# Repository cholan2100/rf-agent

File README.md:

# RF Agent

An autonomous AI RF/Microwave hardware engineering engine and PCB design suite.

> [!IMPORTANT]
> **AI Harness Native**: This project is explicitly designed to be used inside an AI Agent Harness environment (such as Google's Antigravity, Cursor, Claude Code, GitHub Copilot Workspace, OpenDevin, etc.). 
> 
> **Intended Workflow**:
> 1. Check out this repository inside your AI harness.
> 2. Ask the harness agent to design an RF PCB (e.g., "Design a 10dB 2.4GHz Attenuator").
> 3. The agent will read the provided instructions (`AGENTS.md` / `SKILLS.md`), follow the 9-stage engineering protocol, and synthesize the schematics, route the layout, and run the simulations autonomously.

`rf-agent` enables AI coding agents to autonomously synthesize schematics, route controlled-impedance coplanar waveguides, perform headless DRC verification, execute 3D electromagnetic FDTD simulations, and generate production-ready Gerber archives and raytraced 3D visualizations.

---

## Quickstart

In your preferred AI agent harness (Antigravity, Cursor, Claude Code, OpenCode, Codex, GitHub Copilot, Windsurf, Roo Code), paste the following prompt into the chat:

```text
Clone https://github.com/cholan2100/rf-agent.git with submodules and Initialize the agent as per governing files in this repository.
```

> [!TIP]
> If you have already cloned the repository and opened the workspace folder inside your harness, you can simply prompt:
> ```text
> Initialize the agent as per governing files in this repository.
> ```

---

## How it Works

The autonomous RF hardware engineering pipeline operates as a synergistic triad:

* **AI Agent Harness**: Provides intelligence using any LLM model (e.g., Claude, Gemini, GPT, DeepSeek) within your environment (such as Antigravity, Cursor, Claude Code, OpenCode, Codex, GitHub Copilot, Roo Code).
* **`rf-agent` (This Repository)**: Guides the Agent to execute the engineering workflow step by step per governing protocols (`AGENTS.md` / `SKILLS.md`), synthesizing schematics, calculating passive component values, and formulating controlled-impedance layout specifications.
* **`rf-suite` (Cloud SaaS or Local Dockerized)**: Provides the tools necessary to do the tasks—supplying headless KiCad 10, FreeCAD 1.0, openEMS 3D FDTD, Qucsator-RF, and ngspice solvers either via the hosted AWS SaaS microservice (`http://rf.nakedcircuits.com:8000`) or inside a local Docker container.

---

## Toolchain Architecture: Dependency on `rf-suite`

`rf-agent` is structured as a decoupled, two-tier architecture separating **AI Agent Design Intellect** from the **Heavy EDA & Solver Toolchain**:

```
┌────────────────────────────────────────────────────────────────────────┐
│                          rf-agent (This Repo)                          │
│                   AI Agent Intellect & Workflow Core                   │
│  - Circuit Spec Synthesis (spec.py) & Passive Math (Pi, Tank, BPF, SOLT)│
│  - Programmatic KiCad 10 Schematic & Layout Routing (agent/pcb_gen.py) │
│  - Controlled-Impedance CPWG Math, Tapers, & Via Fencing Synthesis     │
│  - Automated Headless 9-Stage Pipeline Orchestrator (agent/workflow.py) │
│  - Interactive Human-in-the-Loop Review Protocols & Popups             │
└───────────────────────────────────┬────────────────────────────────────┘
                                    │ invokes via rf-suite/bin launchers
                                    ▼
┌────────────────────────────────────────────────────────────────────────┐
│                        rf-suite (Linked Submodule)                     │
│               Containerized Multi-Physics Engineering Stack            │
│  - KiCad 10.0.4: pcbnew Python C++ bindings, kicad-cli, 3D Raytracer   │
│  - FreeCAD 1.0.0: FreeCADCmd, Microwave Workbench, STEP Exporter      │
│  - openEMS v0.37.0-rc2: 3D FDTD Full-Wave EM Solver & CSXCAD API       │
│  - Qucs-S 24.4.1 & qucsator-rf 1.0.3: Linear S-Parameter Co-Simulation │
│  - ngspice 44.2: Non-linear SPICE DC bias & transient sweeps           │
│  - RF Python Stack: scikit-rf, numpy, scipy, matplotlib, cairosvg      │
│  - X11 / noVNC Web Desktop: Interactive visual GUI on port 6080       │
└────────────────────────────────────────────────────────────────────────┘
```

The underlying toolchain is linked as a Git submodule at `./rf-suite` pointing to [`cholan2100/rf-suite`](https://github.com/cholan2100/rf-suite). This guarantees that neither developers nor autonomous agents need to manually compile or install gigabytes of complex C++ EDA tools on the host system.

---

## Docker Environment & Host OS Architecture

The Docker container daemon location depends on the host operating system:
- **Windows**: Docker is by default found and hosted inside the **WSL Debian** environment (`wsl -d Debian`). When running Docker commands directly on Windows, execute them via WSL: `wsl -d Debian bash -c "docker ..."`. The Windows batch scripts in `rf-suite\bin\` (`rf-run.bat`, `rf-bash.bat`, `rf-gui.bat`) automatically detect this and target the WSL Debian container environment.
- **Linux**: Docker is typically native and accessible directly in the standard system PATH (`docker ...`).

---

## Repository Self-Provisioning Protocol for Agents

Autonomous agents and automated CI runners must adhere to the **Turn 0 Self-Provisioning Protocol** (canonical, detailed version: [`AGENTS.md` §1.2](AGENTS.md)):

0. **Step 0 — Automatic `.env` Bootstrapping**:
   If `.env` does not exist (e.g. fresh clone), the agent automatically creates it configured for the local containerized toolchain with **zero AWS credentials**:
   ```ini
   # RF Agent Toolchain Configuration
   RF_BACKEND=local
   RF_SAAS_URL=http://rf.nakedcircuits.com:8000
   RF_WAKE_URL=https://rfhealth.nakedcircuits.com
   ```
   Users do not need to configure AWS credentials. When the local Docker toolchain is active, all solvers run locally inside `rf-suite`.

1. **Gate 1 — Submodule Initialization**:
   A fresh `git clone` does **not** check out submodules by default, so `rf-suite/` will be empty and the launchers will be missing. Verify and bootstrap:
   ```bash
   # Verify (portable, non-fatal):
   git submodule status rf-suite   # must NOT start with a '-'
   # Or check for the launcher directly:
   ls rf-suite/bin/rf-run          # Windows: ls rf-suite\bin\rf-run.bat

   # If missing, initialize and verify:
   git submodule update --init --recursive
   ```
   > Tip for users: cloning with `git clone --recurse-submodules https://github.com/cholan2100/rf-agent.git` pre-satisfies Gate 1.

2. **Gate 2 — Execution Backend Readiness Verification**:
   The default execution backend is **Direct Local Commands** (`RF_BACKEND=local`), running KiCad 10, FreeCAD 1.0, openEMS, and Qucsator inside the containerized `rf-suite` Docker environment.
   - **SaaS Availability Probe**: The agent checks if the cloud SaaS API service (`http://rf.nakedcircuits.com:8000/health`) is online and healthy.
   - **If the SaaS API service is unavailable**: The agent does **not** use or announce the SaaS service to the user, and silently defaults directly to the local dockerized `rf-suite` (`RF_BACKEND=local`).
   - **If the SaaS API service is verified online & healthy**: The agent may offer the option to offload compute via cloud SaaS (`RF_BACKEND=aws_saas`).

   If Direct Local execution is chosen and the Docker image is missing, the agent triggers the build:
   ```bash
   # On Windows (Docker in WSL Debian): compute the WSL path of <repo-root> first
   # (e.g. D:\Workspace\rf\rf-agent -> /mnt/d/Workspace/rf/rf-agent), then:
   wsl -d Debian bash -c "cd <wsl-path-of-repo-root>/rf-suite && docker compose build"
   # Or if native Docker CLI is in Windows PATH:
   cd rf-suite && docker compose build

   # On Linux (Native Docker):
   cd rf-suite && docker compose build
   ```
   When the build finishes, the agent notifies the user:
   > *"The `rf-suite` Docker environment has been built and verified! Proceeding to Gate 3..."*

3. **Gate 3 — Mandatory Final Invitation Greeting**:
   Once Gates 1 and 2 pass:
   - **Every time the repository is used to initialize the agent**, the agent concludes its initialization turn by presenting the final invitation greeting asking what RF circuit to design today, with concrete example prompts (e.g. *"Bandpass filter for 98mhz FM Radio band using parallel LC tank"*, *"Low Noise amplifier for 137MHz satellite band"*, 10dB attenuator, 50Ω calibration load, etc.; see [`AGENTS.md` §1.2](AGENTS.md)).
   - If a circuit design was already specified upfront, the agent delivers the greeting and proceeds immediately to Task 1 (Schematic Synthesis).

---

## Key Capabilities

- **Autonomous AI Agent Native**: Orchestrated by `agent.workflow` with programmatic KiCad (`pcbnew`), FreeCAD, openEMS, and Qucsator interfaces for complete headless hardware design.
- **Controlled-Impedance Synthesis**: Grounded Coplanar Waveguide (CPWG) synthesis with closed-form conformal mapping equations for 50Ω transmission lines, 45° neckdown tapers, and ground via fences.
- **Multi-Port & 1-Port Support**: Full support for 2-port circuits (filters, attenuators, power dividers) and dedicated 1-port termination/calibration standards (loads, shorts, opens) with single-ended Return Loss ($S_{11}$) and VSWR verification.
- **Headless Design Rule Checks (DRC)**: Automated zero-tolerance DRC audits verifying 0 violations and 0 warnings prior to fabrication export.
- **Photorealistic Raytraced 3D Renders**: Headless multi-angle board rendering (Isometric, Top, Bottom) with component 3D packages using KiCad 10's native CLI raytracer.
- **Full-Wave 3D EM & Circuit Co-Simulation**: openEMS FDTD solver extraction yielding Touchstone `.s2p` / `.s1p` matrices, co-simulated with Qucsator in a standard 50Ω system.
- **Fabrication Packaging**: Production-grade RS-274X Gerber & Excellon NC drill ZIP packages, vector SVGs, 3D STEP mechanical assemblies, and engineering markdown reports with BOMs.

---

## Manual CLI Verification & Reference Execution

### 1. Clone & Initialize Submodule
```bash
git clone --recurse-submodules https://github.com/cholan2100/rf-agent.git
cd rf-agent

# If already cloned without submodules:
git submodule update --init --recursive
```

### 2. Verify Toolchain Environment
Run the 14-point diagnostic suite using the `rf-suite` launcher:
```bash
# On Windows:
rf-suite\bin\rf-run.bat python tests/verify_environment.py

# On Linux / WSL:
./rf-suite/bin/rf-run python3 tests/verify_environment.py
```

### 3. Run Reference Example (100MHz LC Bandpass Filter)
Synthesize, verify DRC, generate production Gerbers, STEP model, and 3D raytrace:
```bash
# On Windows:
rf-suite\bin\rf-run.bat python -m agent.workflow --desc "BPF for 100mhz center with LC tank parallel shunt"

# On Linux / WSL:
./rf-suite/bin/rf-run python3 -m agent.workflow --desc "BPF for 100mhz center with LC tank parallel shunt"
```

---

## Workflow Architecture

The automated pipeline consists of 9 sequential, modular stages:

```
┌─────────────────────────────────────────────────────────────┐
│ 1. KiCad 10 Schematic & Zoomed Vector Crop (schematic)      │
│    Generates .kicad_sch, exports SVG, renders high-DPI crop │
└──────────────────────────────┬──────────────────────────────┘
                               ▼
┌─────────────────────────────────────────────────────────────┐
│ 2. Controlled Impedance PCB Layout & DRC (pcb)              │
│    Collinear CPWG routing, 45° tapers, zone refill & DRC    │
└──────────────────────────────┬──────────────────────────────┘
                               ▼
┌─────────────────────────────────────────────────────────────┐
│ 3. Photorealistic 3D Raytraced Visualizations (render)      │
│    Raytraces Isometric, Top, and Bottom views with passives │
└──────────────────────────────┬──────────────────────────────┘
                               ▼
┌─────────────────────────────────────────────────────────────┐
│ 4. Native Mechanical CAD Project & 3D STEP Assembly (cad)   │
│    Generates .FCStd and exports standard mechanical .step   │
└──────────────────────────────┬──────────────────────────────┘
                               ▼
┌─────────────────────────────────────────────────────────────┐
│ 5. Multi-Port S-Parameter EM Extraction (em)                │
│    Simulates high-frequency response -> Touchstone (.sNp)   │
└──────────────────────────────┬──────────────────────────────┘
                               ▼
┌─────────────────────────────────────────────────────────────┐
│ 6. Qucs-S Co-Simulation Engine Execution (qucs)             │
│    Co-simulates Touchstone block in 50Ω system netlist      │
└──────────────────────────────┬──────────────────────────────┘
                               ▼
┌─────────────────────────────────────────────────────────────┐
│ 7. Publication-Quality RF Performance Plots (charts)        │
│    Plots S-Parameters (dB), Smith Chart, Stability K, Zin   │
└──────────────────────────────┬──────────────────────────────┘
                               ▼
┌─────────────────────────────────────────────────────────────┐
│ 8. Production Gerber & Drill ZIP Packaging (gerbers)        │
│    Packages 26-layer Gerber and drill archive               │
└──────────────────────────────┬──────────────────────────────┘
                               ▼
┌─────────────────────────────────────────────────────────────┐
│ 9. Comprehensive Performance Report & BOM (report)          │
│    Compiles PERFORMANCE_REPORT.md with margin analysis      │
└─────────────────────────────────────────────────────────────┘
```

---

## CLI Usage (Reference Only)

> [!IMPORTANT]
> **Not for Manual Execution**
> The following CLI commands are provided strictly for reference, debugging, and to show how the autonomous AI agents interact with the internal tools. Manual CLI usage by human engineers is **not** the intended use case. This project is explicitly designed to be driven entirely by an AI Agent Harness environment.

All workflow stages are invoked by the autonomous agents using the cross-platform launchers in `rf-suite/bin/`:

### Stage-by-Stage Modular Execution
Run individual stages to review deliverables interactively between steps:

#### Windows (PowerShell / CMD)
```cmd
:: Task 1: Schematic Synthesis & Zoomed Crop
rf-suite\bin\rf-run.bat python -m agent.workflow --desc "50 ohm Load circuit for calibration" --stages schematic

:: Task 2: Controlled Impedance PCB Layout & DRC
rf-suite\bin\rf-run.bat python -m agent.workflow --spec-file projects/calibration_load_50ohm/spec.json --stages pcb

:: Task 3: 3D Raytracing (Iso, Top, Bottom)
rf-suite\bin\rf-run.bat python -m agent.workflow --spec-file projects/calibration_load_50ohm/spec.json --stages render

:: Task 4: Mechanical CAD & 3D STEP Assembly
rf-suite\bin\rf-run.bat python -m agent.workflow --spec-file projects/calibration_load_50ohm/spec.json --stages cad

:: Task 5: openEMS EM Simulation -> Touchstone .s1p / .s2p
rf-suite\bin\rf-run.bat python -m agent.workflow --spec-file projects/calibration_load_50ohm/spec.json --stages em

:: Task 6: Qucs-S Co-Simulation
rf-suite\bin\rf-run.bat python -m agent.workflow --spec-file projects/calibration_load_50ohm/spec.json --stages qucs

:: Task 7: RF Performance Charts
rf-suite\bin\rf-run.bat python -m agent.workflow --spec-file projects/calibration_load_50ohm/spec.json --stages charts

:: Task 8: Production Gerber ZIP
rf-suite\bin\rf-run.bat python -m agent.workflow --spec-file projects/calibration_load_50ohm/spec.json --stages gerbers

:: Task 9: Performance Documentation & BOM
rf-suite\bin\rf-run.bat python -m agent.workflow --spec-file projects/calibration_load_50ohm/spec.json --stages report
```

#### Linux / WSL
```bash
# Task 1: Schematic Synthesis & Zoomed Crop
./rf-suite/bin/rf-run python3 -m agent.workflow --desc "50 ohm Load circuit for calibration" --stages schematic

# Task 2: Controlled Impedance PCB Layout & DRC
./rf-suite/bin/rf-run python3 -m agent.workflow --spec-file projects/calibration_load_50ohm/spec.json --stages pcb

# Task 3: 3D Raytracing (Iso, Top, Bottom)
./rf-suite/bin/rf-run python3 -m agent.workflow --spec-file projects/calibration_load_50ohm/spec.json --stages render

# Task 4: Mechanical CAD & 3D STEP Assembly
./rf-suite/bin/rf-run python3 -m agent.workflow --spec-file projects/calibration_load_50ohm/spec.json --stages cad

# Task 5: openEMS EM Simulation -> Touchstone .s1p / .s2p
./rf-suite/bin/rf-run python3 -m agent.workflow --spec-file projects/calibration_load_50ohm/spec.json --stages em

# Task 6: Qucs-S Co-Simulation
./rf-suite/bin/rf-run python3 -m agent.workflow --spec-file projects/calibration_load_50ohm/spec.json --stages qucs

# Task 7: RF Performance Charts
./rf-suite/bin/rf-run python3 -m agent.workflow --spec-file projects/calibration_load_50ohm/spec.json --stages charts

# Task 8: Production Gerber ZIP
./rf-suite/bin/rf-run python3 -m agent.workflow --spec-file projects/calibration_load_50ohm/spec.json --stages gerbers

# Task 9: Performance Documentation & BOM
./rf-suite/bin/rf-run python3 -m agent.workflow --spec-file projects/calibration_load_50ohm/spec.json --stages report
```

---

## Interactive Web Desktop (noVNC)

For visual inspection of KiCad schematics/PCBs, FreeCAD 3D models, or AppCSXCAD meshes:
- **Windows**: Run `rf-suite\bin\rf-gui.bat`
- **Linux/WSL**: Run `./rf-suite/bin/rf-gui`
- Open browser at **`http://localhost:6080/vnc.html`** (default password: `rfworkbench` if prompted).

---

## Project Structure

```
rf-agent/
├── agent/                          # Autonomous RF workflow engine
│   ├── __init__.py
│   ├── workflow.py                 # Master 9-stage orchestrator
│   ├── spec.py                     # Circuit spec models, synthesis, RF math
│   ├── schematic_gen.py            # KiCad 10 schematic synthesis & SVG export
│   ├── pcb_gen.py                  # CPWG layout, 45° tapers, zone fill & DRC
│   ├── renderer.py                 # Headless raytraced 3D renders (Iso, Top, Bottom)
│   ├── freecad_gen.py              # FreeCAD parametric modeling & STEP assembly
│   ├── em_solver.py                # openEMS FDTD solver & Touchstone .sNp export
│   ├── qucs_sim.py                 # Qucsator linear circuit co-simulation
│   ├── chart_gen.py                # S-parameters & Smith chart plotting
│   ├── gerber_pack.py              # RS-274X Gerber & NC drill ZIP packager
│   └── report_gen.py               # PERFORMANCE_REPORT.md & BOM generator
├── .agents/skills/rf-agent/        # AI Agent skill definition (SKILL.md)
├── projects/                       # Generated design projects & deliverables
├── examples/                       # Automated reference examples
│   └── bpf_100mhz_lc/              # Reference 100MHz LC bandpass filter project
├── tests/                          # Workflow unit tests & diagnostics
│   ├── test_workflow.py            # Headless workflow engine tests
│   └── verify_environment.py       # 14-point EDA/solver diagnostic suite
├── rf-suite/                       # Linked Git submodule: EDA/solver container (cholan2100/rf-suite)
│   ├── bin/                        # Cross-platform launchers (rf-run, rf-bash, rf-gui)
│   ├── docker-compose.yml          # Container configuration
│   └── Dockerfile                  # Container toolchain definition
├── AGENTS.md                       # Autonomous agent operating handbook (Agentic AI Standard)
├── SKILLS.md                       # RF engineering skills catalog
├── .gitmodules                     # Git submodule configuration
├── requirements.txt                # Python RF & scientific dependencies
└── README.md
```

---

## Quality Assurance & Verification

Every design synthesized by `rf-agent` is verified against strict RF engineering criteria:
- **0 DRC Violations**: Clearances, track widths, and zone connectivity audited via `kicad-cli`.
- **50Ω Impedance Matching**: CPWG dimensions verified with coplanar ground clearances ($w = 1.87\text{ mm}$, $s = 0.40\text{ mm}$ on 1.6mm FR4).
- **Component Sourcing**: Industry-standard high-Q RF SMD components (Samtec SMA edge-mount connectors, Coilcraft/Murata 0603 inductors).
- **1-Port Circuit Integrity**: True single-port architecture without phantom output paths or symmetric component duplication.

---

## License

This project is licensed under the [MIT License](LICENSE).

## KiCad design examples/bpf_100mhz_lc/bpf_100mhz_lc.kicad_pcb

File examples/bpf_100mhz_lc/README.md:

# 100MHz LC Tank Bandpass Filter (Autonomously Generated by RF-Agent)

This reference example was designed and generated **fully autonomously** by the `rf-agent` AI. No human intervention, pre-made template files, or manual GUI clicking were involved in the CAD creation or solver execution. The agent interpreted a natural language prompt, mathematically derived the circuit specifications, and drove the 9-stage engineering toolchain seamlessly.

## Workflow Execution Breakdown

Below is a step-by-step description of the 9-stage process the AI agent executed to generate this design.

### 1. Schematic Synthesis
The agent first interpreted the user request to create a 100MHz bandpass filter, derived the appropriate components (L=100nH, C=25.3pF for a shunt parallel LC tank), and programmatically drafted the KiCad 10 schematic. 

### 2. Controlled Impedance PCB Layout & DRC
Based on the default FR4 substrate parameters, the agent synthesized a 50Ω Grounded Coplanar Waveguide (CPWG) with a trace width of 1.87mm and a gap of 0.40mm. It routed the board, implemented 45-degree component pad tapers to eliminate capacitive steps, placed continuous via fencing along the signal trace, poured the copper ground zones, and ran a headless Design Rule Check (DRC) to ensure 0 errors.

### 3. Photorealistic 3D Rendering
To verify mechanical and spatial constraints, the agent invoked KiCad's headless raytracer to generate multiple photorealistic perspectives of the assembled board.

### 4. Mechanical CAD & STEP Assembly
The agent exported the precise board geometry into a standard 3D mechanical STEP file and packaged it inside a native FreeCAD project (`cad/bpf_100mhz_lc.FCStd`) to enable mechanical engineers to seamlessly design an enclosure.

### 5. Multi-Port EM Extraction (openEMS)
The physical PCB layout was meshed and simulated using the openEMS 3D FDTD solver. The agent extracted the full-wave S-parameters (in Touchstone format) across a broad frequency sweep.

### 6. Linear Co-Simulation (Qucs-S)
The Touchstone EM extraction was piped into Qucsator (via Qucs-S) and co-simulated with the discrete SMD components in a standard 50Ω testbed to characterize the filter's real-world behavior.

### 7. RF Performance Visualization
The agent plotted the resulting dataset using Matplotlib to produce engineering-grade charts, verifying the target center frequency, insertion loss, and return loss.

### 8. Production Gerber Packaging
A complete 26-layer RS-274X Gerber and Excellon NC drill package was synthesized and compressed into a ZIP archive, immediately ready for fabrication.

### 9. Engineering Report & BOM
Finally, the agent generated a comprehensive Markdown performance report (`PERFORMANCE_REPORT.md`), assembling the bill of materials, substrate metrics, and PASS/FAIL threshold checks into a single human-readable document.

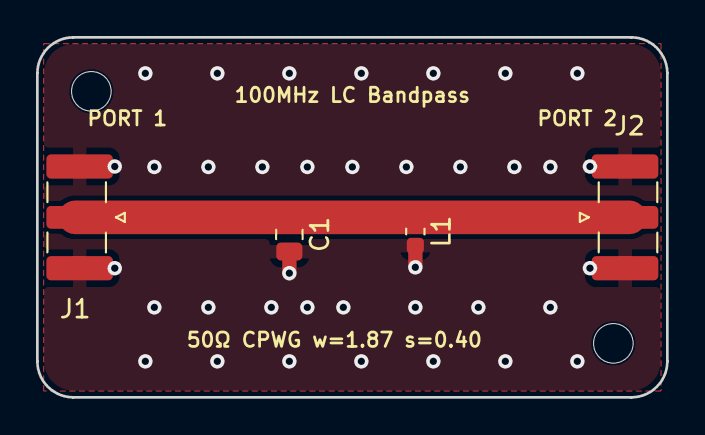
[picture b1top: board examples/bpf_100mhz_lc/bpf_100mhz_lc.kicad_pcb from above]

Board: 2 copper layers, 35.0 x 20.0 mm, 6 parts (0 on the bottom side), 2 nets.

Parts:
C1: 25.3pF; C_0805_2012Metric
H1, H2: MountingHole_2.2mm_M2
J1: SMA_IN; SMA_Samtec_SMA-J-P-H-ST-EM1_EdgeMount
J2: SMA_OUT; SMA_Samtec_SMA-J-P-H-ST-EM1_EdgeMount
L1: 100nH; L_0603_1608Metric

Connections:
GND: C1.2, J1.2, J2.2, L1.2
RF_IN: C1.1, J1.1, J2.1, L1.1

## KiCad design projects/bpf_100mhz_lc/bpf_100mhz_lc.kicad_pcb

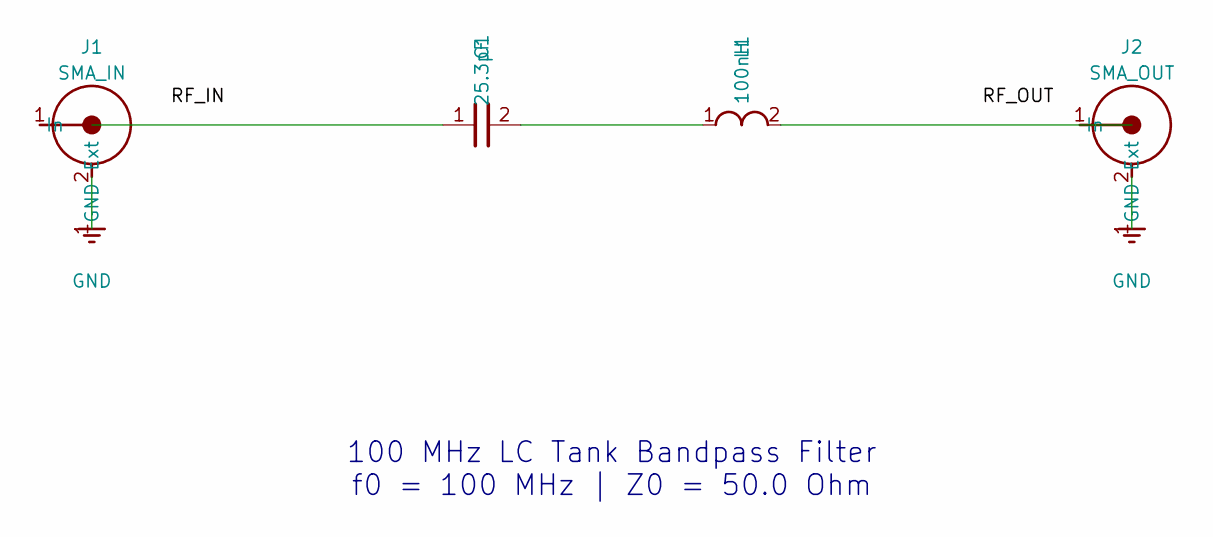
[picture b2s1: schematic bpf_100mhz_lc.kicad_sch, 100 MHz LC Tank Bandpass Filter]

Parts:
C1: 25.3pF; C_0805_2012Metric
J1: SMA_IN
J2: SMA_OUT
L1: 100nH; L_0805_2012Metric

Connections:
GND: J1.2 (Ext), J2.2 (Ext)
NET_MID: C1.2, L1.1
RF_IN: C1.1, J1.1 (In)
RF_OUT: J2.1 (In), L1.2

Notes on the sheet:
100 MHz LC Tank Bandpass Filter f0 = 100 MHz | Z0 = 50.0 Ohm

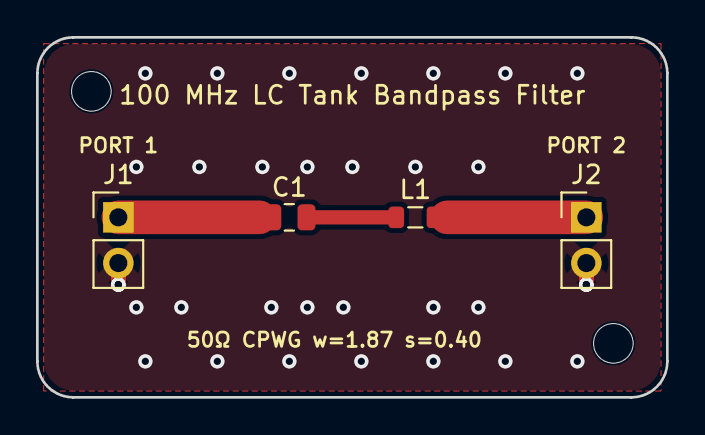
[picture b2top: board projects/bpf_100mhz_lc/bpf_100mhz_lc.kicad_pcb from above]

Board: 2 copper layers, 35.0 x 20.0 mm, 6 parts (0 on the bottom side), 4 nets.

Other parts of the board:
H1, H2: MountingHole_2.2mm_M2

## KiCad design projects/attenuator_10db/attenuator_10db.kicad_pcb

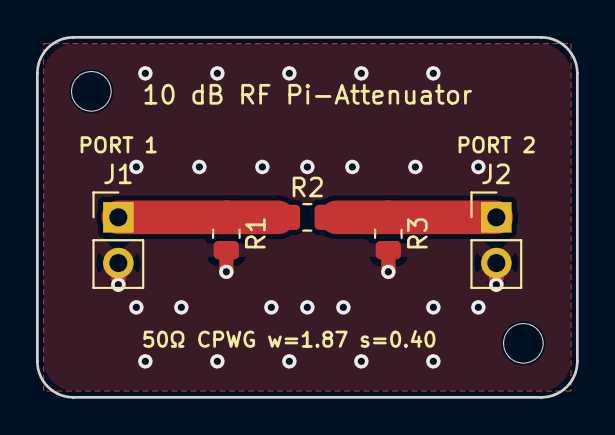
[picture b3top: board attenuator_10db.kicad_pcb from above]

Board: 2 copper layers, 30.0 x 20.0 mm, 7 parts (0 on the bottom side), 3 nets.

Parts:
H1, H2: MountingHole_2.2mm_M2
J1: SMA_IN; PinHeader_1x02_P2.54mm_Vertical
J2: SMA_OUT; PinHeader_1x02_P2.54mm_Vertical
R1, R3: 95.3R; R_0805_2012Metric
R2: 71.5R; R_0805_2012Metric

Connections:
GND: J1.2, J2.2, R1.2, R3.2
RF_IN: J1.1, R1.1, R2.1
RF_OUT: J2.1, R2.2, R3.1

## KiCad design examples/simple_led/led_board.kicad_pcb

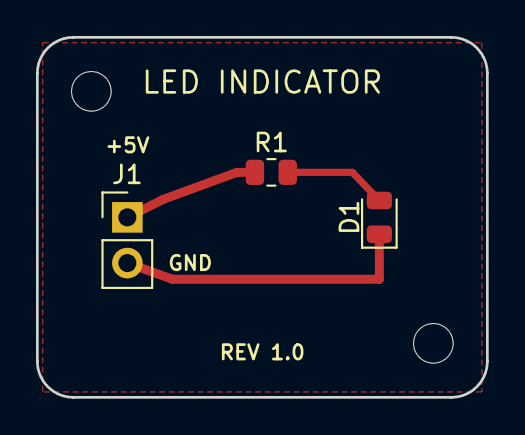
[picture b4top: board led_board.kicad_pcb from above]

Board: 2 copper layers, 25.0 x 20.0 mm, 5 parts (0 on the bottom side), 3 nets.

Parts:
D1: RED_LED; LED_0805_2012Metric
H1, H2: MountingHole_2.2mm_M2
J1: +5V_GND; PinHeader_1x02_P2.54mm_Vertical
R1: 330R; R_0805_2012Metric

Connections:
+5V: J1.1, R1.1
GND: D1.1, J1.2
NET_LED_ANODE: D1.2, R1.2
